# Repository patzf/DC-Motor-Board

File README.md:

# DC-Motor-Board
LA4 Projekt 26/27

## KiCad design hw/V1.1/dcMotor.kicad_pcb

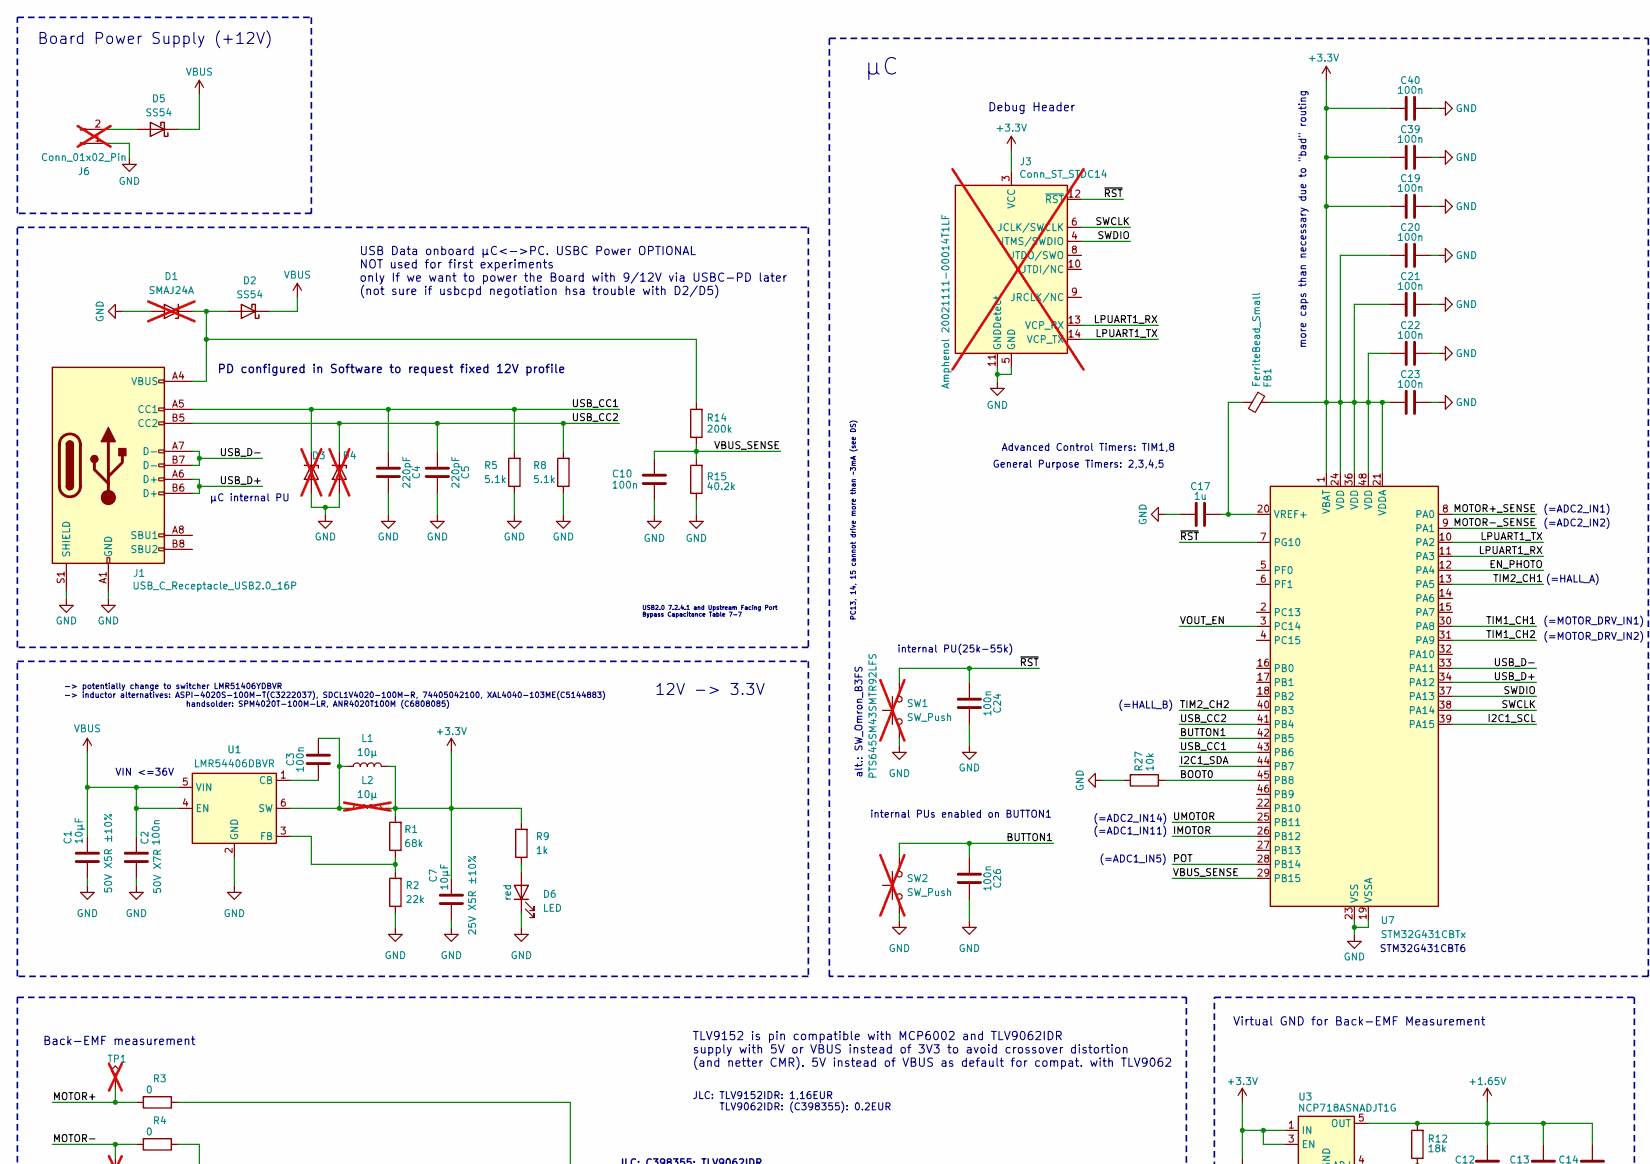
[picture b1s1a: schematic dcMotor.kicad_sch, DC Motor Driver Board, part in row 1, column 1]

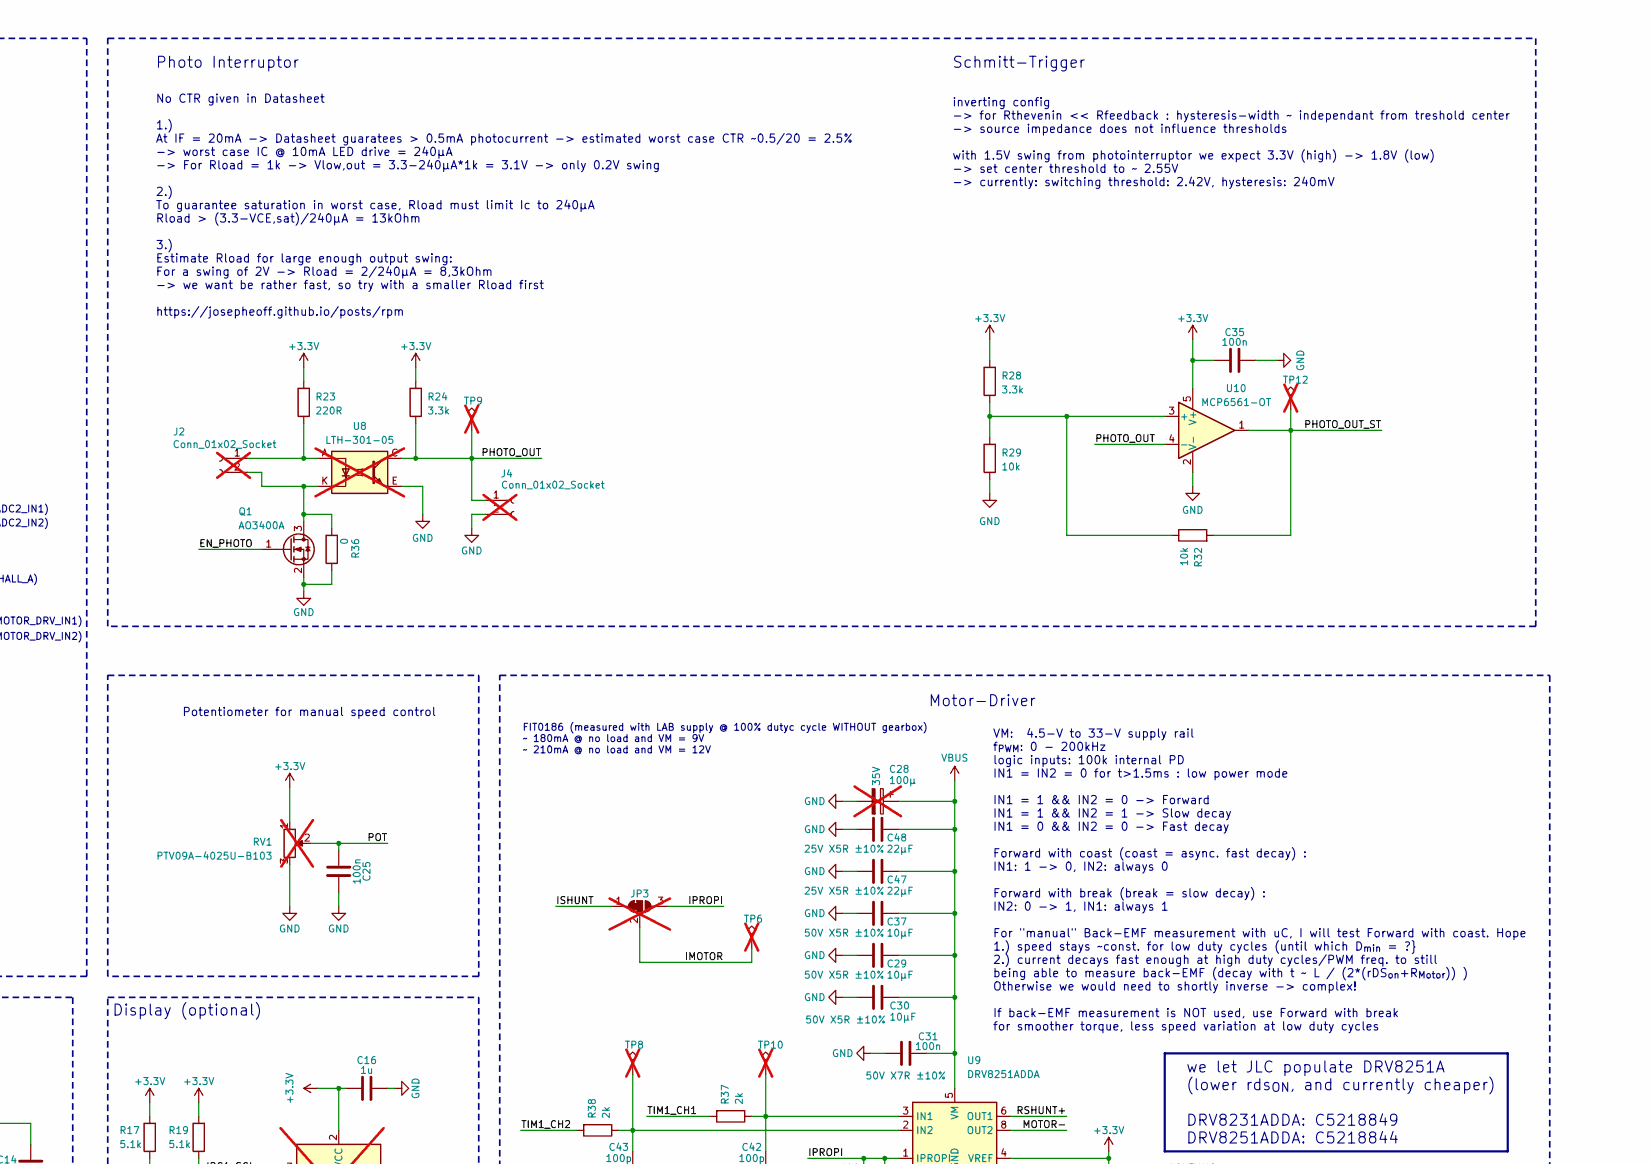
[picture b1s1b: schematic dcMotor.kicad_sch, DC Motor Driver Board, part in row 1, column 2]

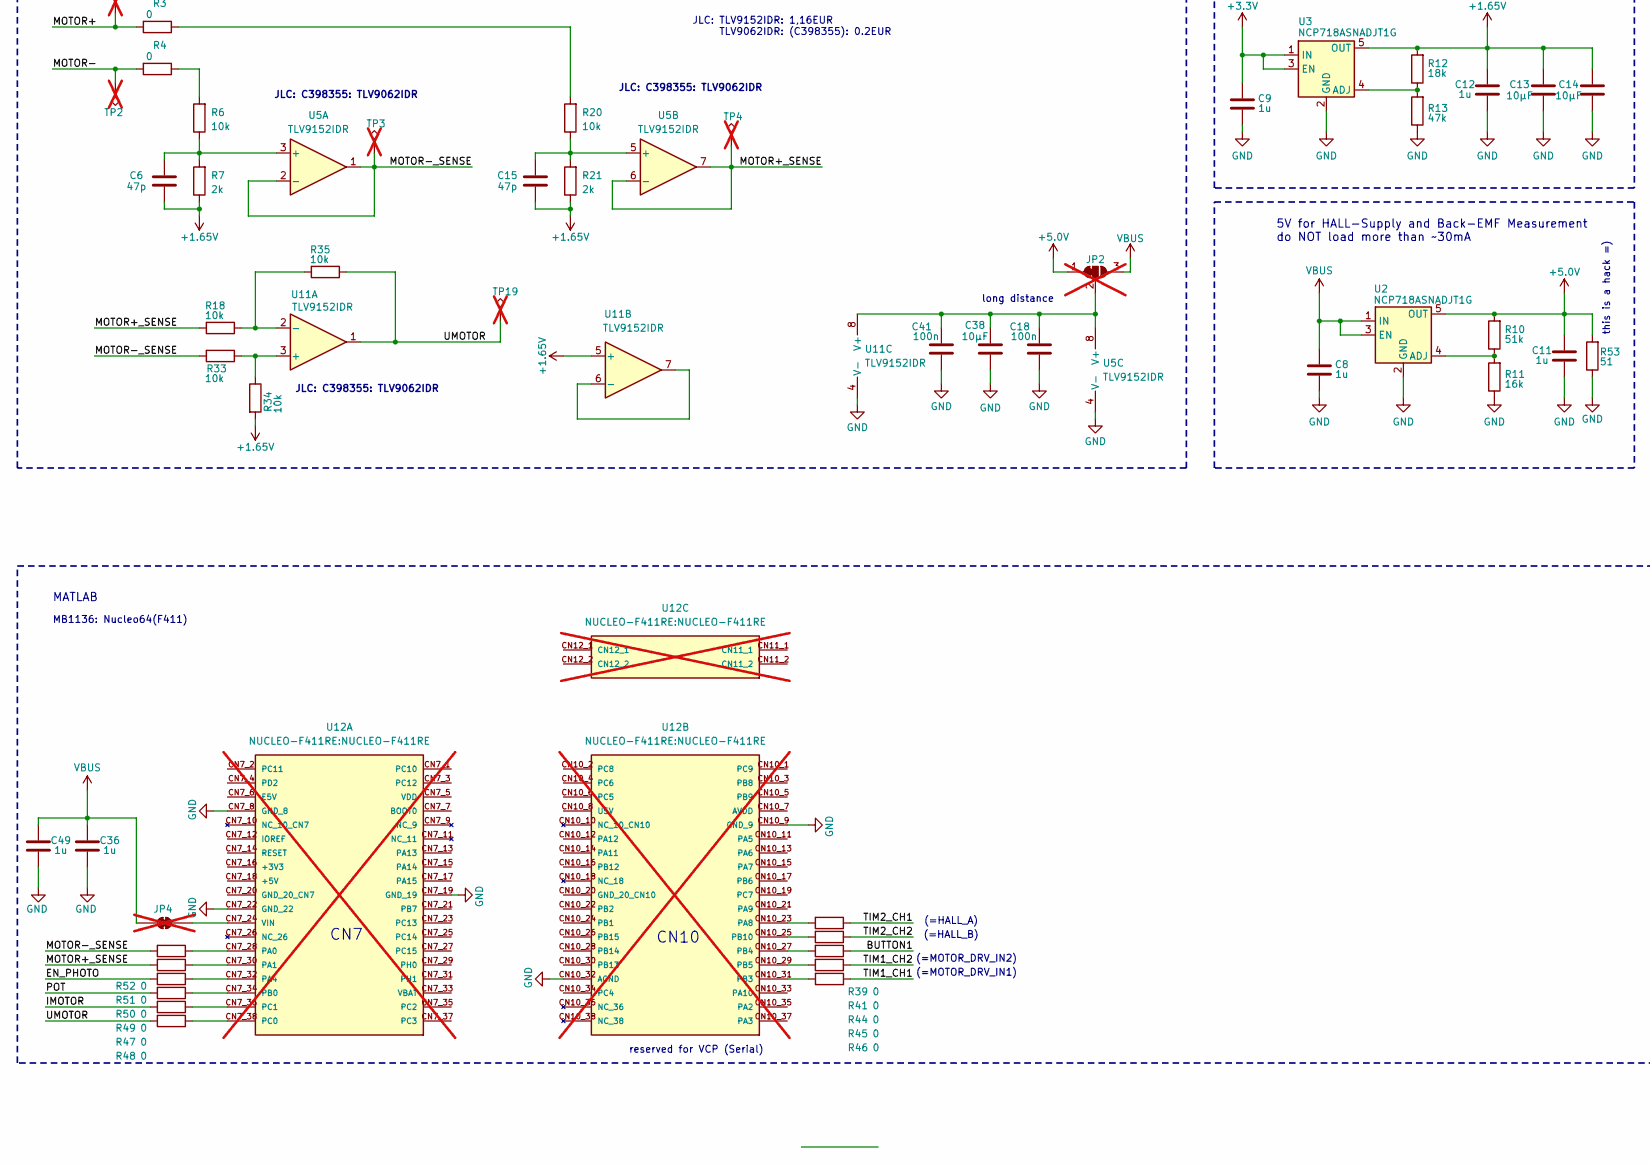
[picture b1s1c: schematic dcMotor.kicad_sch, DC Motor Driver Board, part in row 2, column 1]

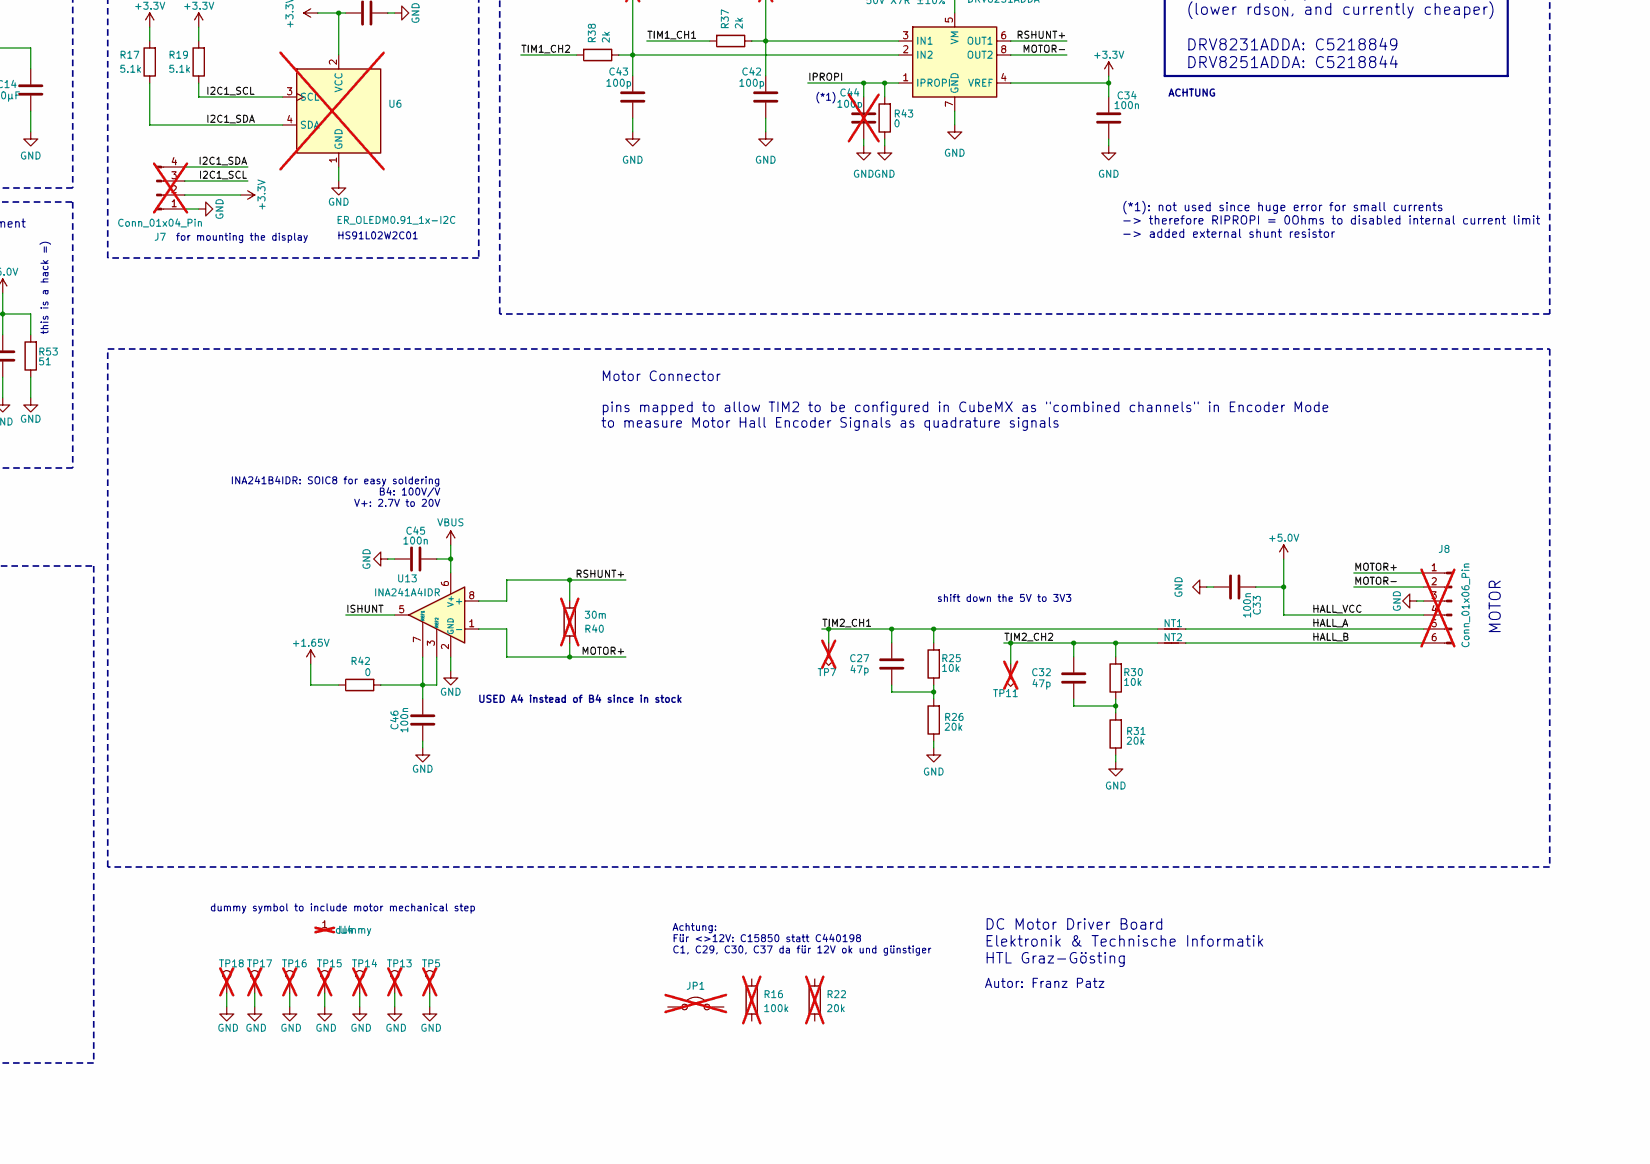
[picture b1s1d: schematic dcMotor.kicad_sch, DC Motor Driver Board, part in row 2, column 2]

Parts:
C1, C29, C30, C37: 10µF; C_0805_2012Metric_Pad1.18x1.45mm_HandSolder; LCSC Part # C15850
C2, C3: 100n; C_0603_1608Metric; LCSC Part # C14663
C4, C5: 220pF; C_0603_1608Metric_Pad1.08x0.95mm_HandSolder; LCSC Part # C1603
C6, C15, C27, C32: 47p; C_0805_2012Metric_Pad1.18x1.45mm_HandSolder; LCSC Part # C14857
C7, C13, C14, C38: 10µF; C_0805_2012Metric; LCSC Part # C15850
C8, C9, C11, C12, C36, C49: 1u; C_0805_2012Metric_Pad1.18x1.45mm_HandSolder; LCSC Part # C28323
C10, C18, C19, C20, C21, C22, C23, C24, C25, C26, C31, C33, C34, C35, C39, C40, C41, C45, C46: 100n; C_0402_1005Metric; LCSC Part # C307331
C16, C17: 1u; C_0402_1005Metric; LCSC Part # C52923
C28: 100µ; CP_Elec_6.3x7.7; LCSC Part # C5145169; not fitted
C42, C43: 100p; C_0805_2012Metric_Pad1.18x1.45mm_HandSolder; LCSC Part # C1790
C44: 100p; C_0805_2012Metric_Pad1.18x1.45mm_HandSolder; LCSC Part # C1790; not fitted
C47, C48: 22µF; C_1206_3216Metric_Pad1.33x1.80mm_HandSolder; LCSC Part # C12891
D1: SMAJ24A; D_SMA; LCSC Part # C132947; not fitted
D2, D5: SS54; D_SMA_Handsoldering; LCSC Part # C22452
D3, D4: ESD5Zxx; D_SOD-523; LCSC Part # C5199848; not fitted
D6: LED; LED_0603_1608Metric_Pad1.05x0.95mm_HandSolder; LCSC Part # C2286
FB1: FerriteBead_Small; R_0603_1608Metric_Pad0.98x0.95mm_HandSolder; LCSC Part # C1002
J1: USB_C_Receptacle_USB2.0_16P; USB_C_Receptacle_HCTL_HC-TYPE-C-16P-01A; LCSC Part # C2894897
J2, J4: Conn_01x02_Socket; PinSocket_1x02_P2.54mm_Vertical; not fitted
J3: Conn_ST_STDC14; PinHeader_2x07_P1.27mm_Vertical; LCSC Part # C3325730; not fitted
J6: Conn_01x02_Pin; PhoenixContact_MSTBVA_2,5_2-G-5,08_1x02_P5.08mm_Vertical; LCSC Part # C480503; not fitted
J7: Conn_01x04_Pin; PinHeader_1x04_P2.54mm_Vertical; LCSC Part # C7430360; not fitted
J8: Conn_01x06_Pin; PinHeader_1x06_P2.54mm_Vertical; not fitted
JP1: Jumper_2_Open; PinHeader_1x02_P2.54mm_Vertical; LCSC Part # C492401; not fitted
JP2, JP3: SolderJumper_3_Bridged12; SolderJumper-3_P1.3mm_Bridged12_RoundedPad1.0x1.5mm_NumberL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; not fitted
JP4: SolderJumper_2_Bridged; SolderJumper-2_P1.3mm_Bridged_RoundedPad1.0x1.5mm; not fitted
L1: 10µ; IND_SPM4020T-100M-LR; LCSC Part # C307805
L2: 10µ; L_Abracon_ASPIAIG-F4020; LCSC Part # C3222037; not fitted
NT1, NT2: NetTie_2; R_0805_2012Metric_Pad1.20x1.40mm_HandSolder; LCSC Part # C17477
Q1: AO3400A; SOT-23; LCSC Part # C20917
R1: 68k; R_0603_1608Metric; LCSC Part # C23231
R2: 22k; R_0603_1608Metric; LCSC Part # C31850
R3, R4, R36, R39, R41, R42, R43, R44, R45, R46, R47, R48, R49, R50, R51, R52: 0; R_0805_2012Metric; LCSC Part # C17477
R5, R8, R17, R19: 5.1k; R_0402_1005Metric; LCSC Part # C25905
R6, R18, R20, R25, R27, R29, R30, R32, R33, R34, R35: 10k; R_0805_2012Metric; LCSC Part # C17414
R7, R21, R37, R38: 2k; R_0805_2012Metric; LCSC Part # C17604
R9: 1k; R_0603_1608Metric; LCSC Part # C21190
R10: 51k; R_0805_2012Metric; LCSC Part # C17737
R11: 16k; R_0805_2012Metric_Pad1.20x1.40mm_HandSolder; LCSC Part # C17490
R12: 18k; R_0805_2012Metric; LCSC Part # C17506
R13: 47k; R_0805_2012Metric_Pad1.20x1.40mm_HandSolder; LCSC Part # C17713
R14: 200k; R_0603_1608Metric_Pad0.98x0.95mm_HandSolder; LCSC Part # C25811
R15: 40.2k; R_0603_1608Metric_Pad0.98x0.95mm_HandSolder; LCSC Part # C12447
R16: 100k; R_0805_2012Metric; LCSC Part # C149504; not fitted
R22: 20k; R_0805_2012Metric; LCSC Part # C4328; not fitted
R23: 220R; R_0805_2012Metric; LCSC Part # C17557
R24, R28: 3.3k; R_0805_2012Metric; LCSC Part # C26010
R26, R31: 20k; R_0805_2012Metric_Pad1.20x1.40mm_HandSolder; LCSC Part # C4328
R40: 30m; R_1206_3216Metric_Pad1.30x1.75mm_HandSolder; not fitted
R53: 51; R_0805_2012Metric; LCSC Part # C17738
RV1: PTV09A-4025U-B103; Potentiometer_Bourns_PTV09A-1_Single_Vertical; not fitted
SW1, SW2: SW_Push; SW_SPST_PTS645Sx43SMTR92; LCSC Part # C221880; not fitted
TP1, TP2, TP3, TP4, TP6, TP7, TP8, TP9, TP10, TP11, TP12, TP19: TP_Keystone_5010; TP_Keystone_5010-5014_Multipurpose; LCSC Part # C2906765; not fitted
TP5, TP13, TP14, TP15, TP16, TP17, TP18: TestPoint_Keystone_5019; TestPoint_Keystone_5019_Miniature; LCSC Part # C238131; not fitted
U1: LMR54406DBVR; SOT-23-6; LCSC Part # C5219316
U2, U3: NCP718ASNADJT1G; SOT-23-5; LCSC Part # C440035
U4: na; not fitted
U5, U11: TLV9152IDR; SOIC-8_3.9x4.9mm_P1.27mm; LCSC Part # C398355
U6: ER_OLEDM0.91_1x-I2C; LCSC Part # C5248081; not fitted
U7: STM32G431CBTx; LQFP-48_7x7mm_P0.5mm; LCSC Part # C529355
U8: LTH-301-05; LCSC Part # C575483; not fitted
U9: DRV8251ADDA; Texas_HTSOP-8-1EP_3.9x4.9mm_P1.27mm_EP2.95x4.9mm_Mask2.4x3.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; LCSC Part # C5218844
U10: MCP6561-OT; SOT-23-5; LCSC Part # C117501
U12: NUCLEO-F411RE:NUCLEO-F411RE; BOARD_NUCLEO-F411RE; not fitted
U13: INA241A4IDR; SOIC-8_3.9x4.9mm_P1.27mm; LCSC Part # C22427873

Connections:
+1.65V: C6.2, C12.2, C13.2, C14.2, C15.2, R7.1, R12.2, R21.1, R34.2, R42.1, U3.5 (OUT), U11.5 (+)
+3.3V: C7.2, C9.2, C16.2, C19.2, C20.2, C21.2, C22.2, C23.2, C34.1, C35.2, C39.2, C40.2, FB1.1, J3.3 (VCC), J7.2, L1.2, L2.2, R1.2, R9.2, R17.2, R19.2, R23.2, R24.2, R28.2, RV1.1, U3.1 (IN), U3.3 (EN), U6.2 (VCC), U7.1 (VBAT), U7.21 (VDDA), U7.24 (VDD), U7.36 (VDD), U7.48 (VDD), U9.4 (VREF), U10.5 (V+)
+5.0V: C11.2, C33.1, J8.4, JP2.1 (A), R10.2, R53.2, U2.5 (OUT)
/BOOT0: R27.1, U7.45 (PB8)
/BUTTON1: C26.2, R44.1, SW2.2, U7.42 (PB5)
/EN_PHOTO: Q1.1 (G), R50.2, U7.12 (PA4)
/HALL_A: J8.5, NT1.2
/HALL_B: J8.6, NT2.2
/I2C1_SCL: J7.3, R19.1, U6.3 (SCL), U7.39 (PA15)
/I2C1_SDA: J7.4, R17.1, U6.4 (SDA), U7.44 (PB7)
/IMOTOR: JP3.2 (C), R47.2, TP6.1 (1_1), U7.26 (PB12)
/IPROPI: C44.1, JP3.3 (B), R43.2, U9.1 (IPROPI)
/ISHUNT: JP3.1 (A), U13.5
/LPUART1_RX: J3.13 (VCP_RX), U7.11 (PA3)
/LPUART1_TX: J3.14 (VCP_TX), U7.10 (PA2)
/MOTOR+: J8.1, R3.2, R40.2, TP1.1 (1_1), U13.1 (-)
/MOTOR+_SENSE: R18.2, R51.2, TP4.1 (1_1), U5.6 (-), U5.7, U7.8 (PA0)
/MOTOR-: J8.2, R4.2, TP2.1 (1_1), U9.8 (OUT2)
/MOTOR-_SENSE: R33.2, R52.2, TP3.1 (1_1), U5.1, U5.2 (-), U7.9 (PA1)
/PHOTO_OUT: J4.1, R24.1, TP9.1 (1_1), U8.C, U10.4 (-)
/PHOTO_OUT_ST: R32.2, TP12.1 (1_1), U10.1
/POT: C25.2, R49.2, RV1.2, U7.28 (PB14)
/RSHUNT+: R40.1, U9.6 (OUT1), U13.8 (+)
/SWCLK: J3.6 (JCLK/SWCLK), U7.38 (PA14)
/SWDIO: J3.4 (JTMS/SWDIO), U7.37 (PA13)
/TIM1_CH1: R37.2, R46.1, U7.30 (PA8)
/TIM1_CH2: R38.2, R45.1, U7.31 (PA9)
/TIM2_CH1: C27.1, NT1.1, R25.2, R39.1, TP7.1 (1_1), U7.13 (PA5)
/TIM2_CH2: C32.1, NT2.1, R30.2, R41.1, TP11.1 (1_1), U7.40 (PB3)
/UMOTOR: R35.1, R48.2, TP19.1 (1_1), U7.25 (PB11), U11.1
/USB_CC1: C4.2, D3.1 (K), J1.A5 (CC1), R5.2, U7.43 (PB6)
/USB_CC2: C5.2, D4.1 (K), J1.B5 (CC2), R8.2, U7.41 (PB4)
/USB_D+: J1.A6 (D+), J1.B6 (D+), U7.34 (PA12)
/USB_D-: J1.A7 (D-), J1.B7 (D-), U7.33 (PA11)
/VBUS_SENSE: C10.1, R14.1, R15.2, U7.29 (PB15)
/VOUT_EN: U7.3 (PC14)
/~RST: C24.2, J3.12 (~RST), SW1.2, U7.7 (PG10)
GND: C1.2, C2.1, C4.1, C5.1, C7.1, C8.1, C9.1, C10.2, C11.1, C12.1, C13.1, C14.1, C16.1, C17.2, C18.1, C19.1, C20.1, C21.1, C22.1, C23.1, C24.1, C25.1, C26.1, C28.2, C29.2, C30.2, C31.2, C33.2, C34.2, C35.1, C36.1, C37.2, C38.1, C39.1, C40.1, C41.1, C42.2, C43.2, C44.2, C45.1, C46.1, C47.2, C48.2, C49.1, D1.2 (A2), D3.2 (A), D4.2 (A), D6.1 (K), J1.A1 (GND), J1.A12 (GND), J1.B1 (GND), J1.B12 (GND), J1.S1 (SHIELD), J3.5 (GND), J3.7 (GND), J3.11 (GNDDetect), J4.2, J6.1, J7.1, J8.3, Q1.2 (S), R2.1, R5.1, R8.1, R11.1, R13.1, R15.1, R26.1, R27.2, R29.1, R31.1, R36.1, R43.1, R53.1, RV1.3, SW1.1, SW2.1, TP5.1 (1_1), TP13.1 (1_1), TP14.1 (1_1), TP15.1 (1_1), TP16.1 (1_1), TP17.1 (1_1), TP18.1 (1_1), U1.2 (GND), U2.2 (GND), U3.2 (GND), U5.4 (V-), U6.1 (GND), U7.19 (VSSA), U7.23 (VSS), U7.35 (VSS), U7.47 (VSS), U8.E, U9.7 (GND), U9.9 (GND), U10.2 (V-), U11.4 (V-), U12.CN7_8 (GND_8), U12.CN7_19 (GND_19), U12.CN7_22 (GND_22), U12.CN10_9 (GND_9), U12.CN10_32 (AGND), U13.2 (GND), U13.4 (GND)
unnamed: C27.2, R25.1, R26.2
unnamed: C32.2, R30.1, R31.2
unnamed: D1.1 (A1), D2.2 (A), J1.A4 (VBUS), J1.A9 (VBUS), J1.B4 (VBUS), J1.B9 (VBUS), R14.2
unnamed: D5.2 (A), J6.2
unnamed: D6.2 (A), R9.1
unnamed: J2.1, R23.1, U8.A
unnamed: J2.2, Q1.3 (D), R36.2, U8.K
unnamed: C18.2, C38.2, C41.2, JP2.2 (C), U5.8 (V+), U11.8 (V+)
unnamed: JP4.2 (B), U12.CN7_24 (VIN)
unnamed: R4.1, R6.2
unnamed: R3.1, R20.2
unnamed: C3.2, U1.1 (CB)
unnamed: R1.1, R2.2, U1.3 (FB)
unnamed: C3.1, L1.1, L2.1, U1.6 (SW)
unnamed: R10.1, R11.2, U2.4 (ADJ)
unnamed: R12.1, R13.2, U3.4 (ADJ)
unnamed: C6.1, R6.1, R7.2, U5.3 (+)
unnamed: C15.1, R20.1, R21.2, U5.5 (+)
unnamed: C17.1, FB1.2, U7.20 (VREF+)
unnamed: C42.1, R37.1, TP10.1 (1_1), U9.3 (IN1)
unnamed: C43.1, R38.1, TP8.1 (1_1), U9.2 (IN2)
unnamed: R28.1, R29.2, R32.1, U10.3 (+)
unnamed: R33.1, R34.1, U11.3 (+)
unnamed: R18.1, R35.2, U11.2 (-)
unnamed: U11.6 (-), U11.7
unnamed: R52.1, U12.CN7_28 (PA0)
unnamed: R51.1, U12.CN7_30 (PA1)
unnamed: R50.1, U12.CN7_32 (PA4)
unnamed: R49.1, U12.CN7_34 (PB0)
unnamed: R48.1, U12.CN7_38 (PC0)
unnamed: R47.1, U12.CN7_36 (PC1)
unnamed: R39.2, U12.CN10_23 (PA8)
unnamed: R46.2, U12.CN10_31 (PB3)
unnamed: R44.2, U12.CN10_27 (PB4)
unnamed: R45.2, U12.CN10_29 (PB5)
unnamed: R41.2, U12.CN10_25 (PB10)
unnamed: C46.2, R42.2, U13.3 (REF2), U13.7 (REF1)
VBUS: C1.1, C2.2, C8.2, C28.1, C29.1, C30.1, C31.1, C36.2, C37.1, C45.2, C47.1, C48.1, C49.2, D2.1 (K), D5.1 (K), JP2.3 (B), JP4.1 (A), U1.4 (EN), U1.5 (VIN), U2.1 (IN), U2.3 (EN), U9.5 (VM), U13.6 (V+)

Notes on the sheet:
JLC: C398355: TLV9062IDR
Photo Interruptor
VIN <=36V
dummy symbol to include motor mechanical step
12V -> 3.3V
we let JLC populate DRV8251A (lower rds_{ON}, and currently cheaper) DRV8231ADDA: C5218849 DRV8251ADDA: C5218844
Motor Connector pins mapped to allow TIM2 to be configured in CubeMX as "combined channels" in Encoder Mode to measure Motor Hall Encoder Signals as quadrature signals
USED A4 instead of B4 since in stock
ACHTUNG
(=MOTOR_DRV_IN1)
inverting config -> for Rthevenin << Rfeedback : hysteresis-width ~ independant from treshold center -> source impedance does not influence thresholds with 1.5V swing from photointerruptor we expect 3.3V (high) -> 1.8V (low) -> set center threshold to ~ 2.55V -> currently: switching threshold: 2.42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
PD configured in Software to request fixed 12V profile
TLV9152 is pin compatible with MCP6002 and TLV9062IDR supply with 5V or VBUS instead of 3V3 to avoid crossover distortion (and netter CMR). 5V instead of VBUS as default for compat. with TLV9062
No CTR given in Datasheet 1.) At IF = 20mA -> Datasheet guaratees > 0.5mA photocurrent -> estimated worst case CTR ~0.5/20 = 2.5% -> worst case IC @ 10mA LED drive = 240µA -> For Rload = 1k -> Vlow,out = 3.3-240µA*1k = 3.1V -> only 0.2V swing 2.) To guarantee saturation in worst case, Rload must li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
Schmitt-Trigger
(=ADC2_IN14)
alt.: SW_Omron_B3FS
internal PUs enabled on BUTTON1
5V for HALL-Supply and Back-EMF Measurement do NOT load more than ~30mA
(=ADC1_IN5)
MB1136: Nucleo64(F411)
CN7
µC internal PU
STM32G431CBT6
Display (optional)
shift down the 5V to 3V3
FIT0186 (measured with LAB supply @ 100% dutyc cycle WITHOUT gearbox) ~ 180mA @ no load and VM = 9V ~ 210mA @ no load and VM = 12V
(=HALL_B)
(=HALL_A)
Autor: Franz Patz
-> potentially change to switcher LMR51406YDBVR -> inductor alternatives: ASPI-4020S-100M-T(C3222037), SDCL1V4020-100M-R, 74405042100, XAL4040-103ME(C5144883) handsolder: SPM4020T-100M-LR, ANR4020T100M (C6808085)
Motor-Driver
(=ADC2_IN1)
Back-EMF measurement
internal PU(25k-55k)
INA241B4IDR: SOIC8 for easy soldering B4: 100V/V V+: 2.7V to 20V
PC13, 14, 15 cannot drive more than ~3mA (see DS)
USB Data onboard µC<->PC. USBC Power OPTIONAL NOT used for first experiments only If we want to power the Board with 9/12V via USBC-PD later (not sure if usbcpd negotiation hsa trouble with D2/D5)
Achtung: Für <>12V: C15850 statt C440198 C1, C29, C30, C37 da für 12V ok und günstiger
Potentiometer for manual speed control

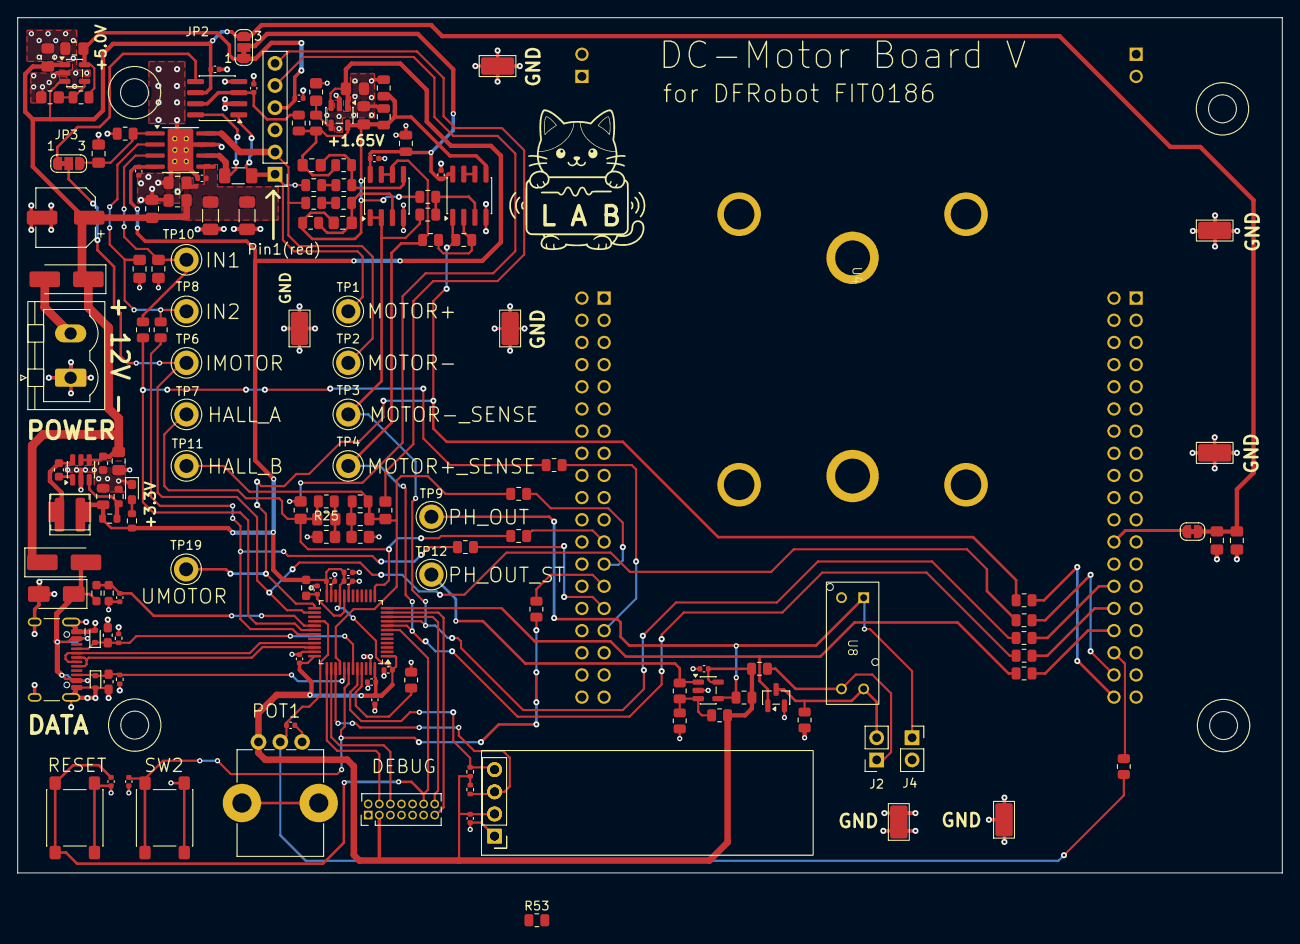
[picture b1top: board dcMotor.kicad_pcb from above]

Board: 2 copper layers, 144.9 x 98.0 mm, 157 parts (1 on the bottom side), 75 nets.

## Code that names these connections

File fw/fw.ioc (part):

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Mcu.Name=STM32G431C(6-8-B)Tx
Mcu.Package=LQFP48
Mcu.UserName=STM32G431CBTx
PA0.Mode=IN1-Differential
PA0.Signal=ADC2_IN1
PA1.Mode=IN1-Differential
PA1.Signal=ADC2_IN2
PA11.Mode=Device
PA11.Signal=USB_DM
PA12.Mode=Device
PA12.Signal=USB_DP
PA13.Mode=Serial_Wire
PA13.Signal=SYS_JTMS-SWDIO
PA14.Mode=Serial_Wire
PA14.Signal=SYS_JTCK-SWCLK
PA15.Mode=I2C
PA15.Signal=I2C1_SCL
PA2.Mode=Asynchronous
PA2.Signal=LPUART1_TX
PA3.Mode=Asynchronous
PA3.Signal=LPUART1_RX
PA4.GPIOParameters=GPIO_Label
PA4.GPIO_Label=EN_PHOTO
PA4.Signal=GPIO_Output
PA5.Signal=S_TIM2_CH1
PA8.Signal=S_TIM1_CH1
PA9.Signal=S_TIM1_CH2
PB11.Mode=IN14-Single-Ended
PB11.Signal=ADC2_IN14
PB12.Mode=IN11-Single-Ended
PB12.Signal=ADC1_IN11
PB14.Mode=IN5-Single-Ended
PB14.Signal=ADC1_IN5
PB15.Mode=IN15-Single-Ended
PB15.Signal=ADC2_IN15
PB3.Signal=S_TIM2_CH2
PB4.Mode=Sink_AllSignals
PB4.Signal=UCPD1_CC2
PB5.GPIOParameters=GPIO_PuPd,GPIO_Label
PB5.GPIO_Label=BUTTON1
PB5.GPIO_PuPd=GPIO_PULLUP
PB5.Signal=GPIO_Input
PB6.Mode=Sink_AllSignals
PB6.Signal=UCPD1_CC1
PB7.Mode=I2C
PB7.Signal=I2C1_SDA
PC14-OSC32_IN.GPIOParameters=GPIO_Label
PC14-OSC32_IN.GPIO_Label=VOUT_EN
PC14-OSC32_IN.Signal=GPIO_Output
RCC.HSE_VALUE=8000000
RCC.SYSCLKFreq_VALUE=160000000
RCC.SYSCLKSource=RCC_SYSCLKSOURCE_PLLCLK
board=custom

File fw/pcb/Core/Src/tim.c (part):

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    __HAL_RCC_GPIOA_CLK_ENABLE();
    __HAL_RCC_GPIOB_CLK_ENABLE();
    /**TIM2 GPIO Configuration
    PA5     ------> TIM2_CH1
    PB3     ------> TIM2_CH2
    */
    GPIO_InitStruct.Pin = GPIO_PIN_5;
    GPIO_InitStruct.Mode = GPIO_MODE_AF_PP;
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
    __HAL_RCC_GPIOA_CLK_ENABLE();
    /**TIM1 GPIO Configuration
    PA8     ------> TIM1_CH1
    PA9     ------> TIM1_CH2
    */
    GPIO_InitStruct.Pin = GPIO_PIN_8|GPIO_PIN_9;
    GPIO_InitStruct.Mode = GPIO_MODE_AF_PP;
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    __HAL_RCC_TIM2_CLK_DISABLE();

    /**TIM2 GPIO Configuration
    PA5     ------> TIM2_CH1
    PB3     ------> TIM2_CH2
    */
    HAL_GPIO_DeInit(GPIOA, GPIO_PIN_5);

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

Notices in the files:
fw/pcb/Core/Src/tim.c:
Copyright (c) 2026 STMicroelectronics.
All rights reserved.
This software is licensed under terms that can be found in the LICENSE file
